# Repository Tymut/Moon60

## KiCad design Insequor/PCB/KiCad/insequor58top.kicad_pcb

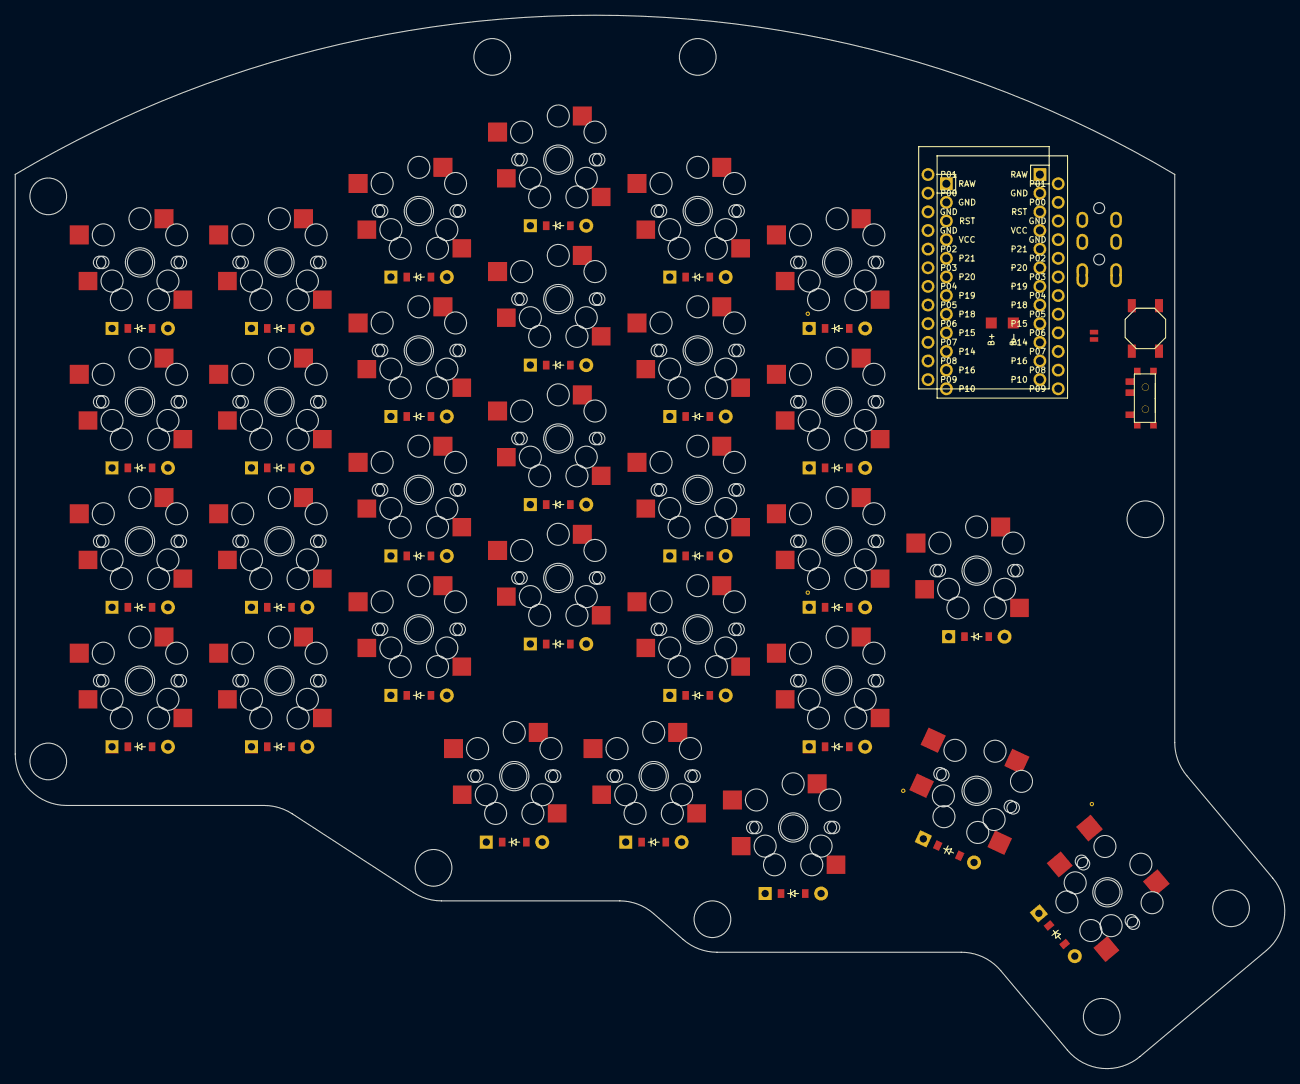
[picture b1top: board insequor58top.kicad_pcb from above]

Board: 2 copper layers, 173.0 x 143.5 mm, 98 parts (0 on the bottom side), 23 nets, no tracks yet.

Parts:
B1: SW_TACT_ALPS_SKQGABE010
D1, D2, D3, D4, D5, D6, D7, D8, D9, D10, D11, D12, D13, D14, D15, D16, D17, D18, D19, D20, D21, D22, D23, D24, D25, D26, D27, D28, D29, D30: ComboDiode
J1, J2: Jumper
MCU1, MCU2: ProMicro
PAD1, PAD2: SMDPad
S1, S3, S5, S7, S9, S11, S13, S15, S17, S19, S21, S23, S25, S27, S29, S31, S33, S35, S37, S39, S41, S43, S45, S47, S49, S51, S53, S55, S57, S59: PG1350
S2, S4, S6, S8, S10, S12, S14, S16, S18, S20, S22, S24, S26, S28, S30, S32, S34, S36, S38, S40, S42, S44, S46, S48, S50, S52, S54, S56, S58, S60: MX
T1: SPDT_C128955

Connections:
Bplus: J1.1, J2.1, PAD1.1
GND: B1.1, MCU1.2, MCU1.15, MCU1.16, MCU2.2, MCU2.15, MCU2.16, PAD2.1, S1.2, S2.2, S3.2, S4.2, S5.2, S6.2, S7.2, S8.2, S9.2, S10.2, S11.2, S12.2, S13.2, S14.2, S15.2, S16.2, S17.2, S18.2, S19.2, S20.2, S21.2, S22.2, S23.2, S24.2, S25.2, S26.2, S27.2, S28.2, S29.2, S30.2, S31.2, S32.2, S33.2, S34.2, S35.2, S36.2, S37.2, S38.2, S39.2, S40.2, S41.2, S42.2, S43.2, S44.2, S45.2, S46.2, S47.2, S48.2, S49.2, S50.2, S51.2, S52.2, S53.2, S54.2, S55.2, S56.2, S57.2, S58.2, S59.2, S60.2
P0: MCU1.14, MCU2.14
P1: MCU1.13, MCU2.13
P2: MCU1.17, MCU2.17
P3: D4.1, D4.2, D8.1, D8.2, D12.1, D12.2, D16.1, D16.2, D20.1, D20.2, D24.1, D24.2, MCU1.18, MCU2.18
P4: D3.1, D3.2, D7.1, D7.2, D11.1, D11.2, D15.1, D15.2, D19.1, D19.2, D23.1, D23.2, MCU1.19, MCU2.19
P5: D2.1, D2.2, D6.1, D6.2, D10.1, D10.2, D14.1, D14.2, D18.1, D18.2, D22.1, D22.2, MCU1.20, MCU2.20
P6: D1.1, D1.2, D5.1, D5.2, D9.1, D9.2, D13.1, D13.2, D17.1, D17.2, D21.1, D21.2, MCU1.21, MCU2.21
P7: D25.1, D25.2, D26.1, D26.2, D27.1, D27.2, D28.1, D28.2, D29.1, D29.2, D30.1, D30.2, MCU1.22, MCU2.22
P8: MCU1.23, MCU2.23
P9: MCU1.24, MCU2.24
P10: MCU1.12, MCU2.12
P14: D21.1, D21.2, D22.1, D22.2, D23.1, D23.2, D24.1, D24.2, D30.1, D30.2, MCU1.10, MCU2.10, S41.1, S42.1, S43.1, S44.1, S45.1, S46.1, S47.1, S48.1, S59.1, S60.1
P15: D17.1, D17.2, D18.1, D18.2, D19.1, D19.2, D20.1, D20.2, D29.1, D29.2, MCU1.9, MCU2.9, S33.1, S34.1, S35.1, S36.1, S37.1, S38.1, S39.1, S40.1, S57.1, S58.1
P16: MCU1.11, MCU2.11
P18: D13.1, D13.2, D14.1, D14.2, D15.1, D15.2, D16.1, D16.2, D28.1, D28.2, MCU1.8, MCU2.8, S25.1, S26.1, S27.1, S28.1, S29.1, S30.1, S31.1, S32.1, S55.1, S56.1
P19: D9.1, D9.2, D10.1, D10.2, D11.1, D11.2, D12.1, D12.2, D27.1, D27.2, MCU1.7, MCU2.7, S17.1, S18.1, S19.1, S20.1, S21.1, S22.1, S23.1, S24.1, S53.1, S54.1
P20: D5.1, D5.2, D6.1, D6.2, D7.1, D7.2, D8.1, D8.2, D26.1, D26.2, MCU1.6, MCU2.6, S9.1, S10.1, S11.1, S12.1, S13.1, S14.1, S15.1, S16.1, S51.1, S52.1
P21: D1.1, D1.2, D2.1, D2.2, D3.1, D3.2, D4.1, D4.2, D25.1, D25.2, MCU1.5, MCU2.5, S1.1, S2.1, S3.1, S4.1, S5.1, S6.1, S7.1, S8.1, S49.1, S50.1
RAW: J1.2, J2.2, MCU1.1, MCU2.1, T1.2
RST: B1.2, MCU1.3, MCU2.3
VCC: MCU1.4, MCU2.4
